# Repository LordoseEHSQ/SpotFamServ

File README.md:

# Spotify Familien Server

Privat gehostetes Familien-Musiksystem: Ein Admin verwaltet Familienprofile mit Spotify-Anbindung, Standard-Lautsprechern und RFID-Karten. Beim Scan einer Karte startet die gebundene Playlist auf dem Profil-Lautsprecher.

## Tech Stack

- **Backend:** Symfony 7.4 (LTS), PHP 8.4+ (Docker-Image/Pi: 8.5.6), Doctrine ORM 3, PostgreSQL 17
- **Frontend:** React 18, TypeScript, Vite, React Router, TanStack Query, React Hook Form
- **Infrastruktur:** Docker Compose (PHP-FPM, Nginx, PostgreSQL)

## Voraussetzungen

- Docker & Docker Compose
- PHP 8.4+ und Composer (für lokale Backend-Entwicklung ohne Docker; Docker-Stack nutzt PHP 8.5.6)
- Node 20+ und pnpm (Frontend)

Für eine frische Raspberry-Pi-Installation siehe `docs/installation.md`.

## Schnellstart

```bash
# Umgebung
cp .env.example .env
# .env anpassen: APP_SECRET, ggf. SPOTIFY_* und DATABASE_URL

# Mit Docker
make up
make migrate

# Backend lokal (ohne Docker-App-Container)
make install-backend
cd backend && php bin/console doctrine:migrations:migrate

# Frontend
make install-frontend
make frontend-dev
```

- **Backend-API:** http://localhost:8080
- **Frontend (Vite):** http://localhost:5173 (Proxy auf Backend)

## Projektstruktur

```
SpotFamServ/
├── backend/          # Symfony modularer Monolith
│   ├── config/
│   ├── migrations/
│   ├── src/Module/   # Admin, FamilyProfile, Spotify, Rfid, Scan, SetupWizard, Shared
│   └── public/
├── frontend/         # React SPA
│   └── src/
│       ├── routes/
│       ├── features/
│       ├── api/
│       └── components/
├── docker/
└── docker-compose.yml
```

## API

REST unter `/api/v1`. Siehe OpenAPI-Dokumentation (geplant) oder `backend/config/routes/`.

## Lizenz

Privat.

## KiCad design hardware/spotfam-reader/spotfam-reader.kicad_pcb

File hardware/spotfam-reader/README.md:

# SpotFam Reader – Platine Rev A

Eigene Platine für den SpotFam-Reader: **ESP32-S3-WROOM-1** direkt bestückt,
USB-C, 3,3-V-Regler, ESD-Schutz, vier Taster, Stecker für den PN532 im
Gehäusedeckel, vorbereitete Display-Anschlüsse (I2C-OLED **oder** SPI-TFT).

> **Status: platziert, nicht fertig geroutet.** Die Dateien wurden ohne KiCad
> generiert. Schaltplan, Netzliste und Pad-Zuordnung sind maschinell gegen
> `tools/design.py` geprüft, ebenso die Abstände der vorverlegten
> Versorgungsbahnen. **Routing der übrigen Netze, ERC und DRC fehlen noch.**
> Vor einer Bestellung unbedingt die Schritte unten durchgehen.

## Dateien

| Datei | Inhalt |
|---|---|
| `tools/design.py` | **Single Source of Truth**: Bauteile, Pins, Netze, LCSC-Nummern |
| `tools/generate.py` | Erzeugt alle Dateien unten (`python3 tools/generate.py`) |
| `tools/pcb.py` | Bestückungsplan (`PLACEMENT`) und vorverlegte Leiterbahnen (`ROUTES`) |
| `footprints/` | Kopien der verwendeten Footprints (KiCad-Bibliothek; ESP32-S3 aus `espressif/kicad-libraries`) |
| `spotfam-reader.kicad_sch` | Schaltplan. Netze hängen über Labels an den Pins |
| `spotfam-reader.kicad_pcb` | Platinenumriss 88,9 × 63,5 mm (Sammelkartenformat, quer), alle Bauteile platziert und mit Netzen, Antennen-Sperrzone, GND-Flächen, vorverlegte 5-V- und 3,3-V-Bahnen |
| `spotfam-reader.kicad_pro` | Projekt mit Netzklassen (Power, USB, Default) und JLCPCB-Regeln |
| `NETLIST.md` | Lesbare Netzliste zum Gegenlesen |
| `bom/jlcpcb-bom.csv` | BOM im JLCPCB-Format (nur SMD-Teile) |
| `bom/full-bom.csv` | Komplette Stückliste inkl. selbst zu lötender Teile |

Bei Änderungen an Pinbelegung oder Bauteilen gilt: `design.py` ändern und
`generate.py` ausführen. Den Schaltplan nicht von Hand umzeichnen, sonst laufen
Doku und KiCad auseinander.

**Achtung:** `generate.py` überschreibt auch `spotfam-reader.kicad_pcb`. Sobald
in KiCad geroutet wurde, ist die `.kicad_pcb` das Original. Danach Änderungen
nur noch in KiCad machen (Schaltplan → **F8**), nicht mehr neu generieren.

## GPIO-Belegung (ESP32-S3)

| Funktion | GPIO | Bemerkung |
|---|---|---|
| USB D− / D+ | 19 / 20 | Nativer USB (Flashen, Serial). Kein USB-UART-Chip nötig |
| Taster NEXT / PREV | 4 / 5 | aktiv LOW gegen GND, `INPUT_PULLUP` |
| Taster VOL+ / VOL− | 6 / 7 | aktiv LOW gegen GND, `INPUT_PULLUP` |
| I2C SDA / SCL | 8 / 9 | PN532 **und** OLED am selben Bus, 4,7 kΩ Pull-ups auf der Platine |
| PN532 IRQ / RSTO | 16 / 17 | optional, im Stecker J2 vorbereitet |
| Status-LED | 15 | über 1 kΩ, aktiv HIGH |
| SPI CS / MOSI / SCK / MISO | 10 / 11 / 12 / 13 | FSPI-Standardpins, nur für TFT |
| TFT DC / RST / BL | 14 / 21 / 47 | nur für TFT. BL direkt am GPIO (max. ca. 20 mA) |
| UART0 TX / RX | 43 / 44 | Debug-Header J5 |
| Frei (J7) | 1, 2, 18, 38 | z. B. Drehencoder |
| BOOT | 0 | Taster SW6 + 10 kΩ Pull-up |
| EN / Reset | EN | Taster SW5, RC 10 kΩ / 1 µF |

Die Strapping-Pins 3, 45 und 46 sind bewusst unbenutzt. GPIO 35–37 bleiben
frei, damit später auch Modulvarianten mit Octal-PSRAM passen.

## Steckverbinder

- **J2 PN532** (JST-XH 6-polig): 1 GND · 2 3V3 · 3 SDA · 4 SCL · 5 IRQ · 6 RSTO.
  Den HW-147 mit **3,3 V** versorgen, nicht mit 5 V: Seine I2C-Pegel hängen an
  der Versorgung, und der ESP32-S3 ist nicht 5-V-tolerant. DIP-Schalter am
  HW-147 auf I2C stellen (siehe `docs/hw0-pn532-runbook.md`).
- **J3 OLED** (Stiftleiste 4-polig): P1 · P2 · SCL · SDA.
  Bei OLED-Modulen ist die Reihenfolge von GND und VCC je nach Händler vertauscht. Deshalb:
  - **GND, VCC, SCL, SDA** (häufigste Variante): JP1 1–2 und JP2 1–2 brücken
  - **VCC, GND, SCL, SDA**: JP1 2–3 und JP2 2–3 brücken
  - Erst messen, dann brücken. Pro Jumper immer nur **eine** Seite.
- **J4 TFT** (9-polig): GND · 3V3 · SCK · MOSI · MISO · CS · DC · RST · BL.
  Nur bestücken, wenn ein SPI-TFT kommt. J3 und J4 können parallel genutzt werden.
- **J5 UART**, **J6 Panel-Taster** (parallel zu SW1–SW4, falls die Taster im
  Gehäuse sitzen statt auf der Platine), **J7 Erweiterung**: optional.

## Nächste Schritte in KiCad (7 oder 8)

Alle Bauteile sind platziert und mit Netzen versehen:
- **U1 (ESP32-S3)** mit der Antenne bündig an der Oberkante, darunter eine Sperrzone ohne Kupfer.
- **USB-C (J1)** an der linken Kante, daneben der ESD-Schutz U3.
- **Versorgung (U2, C1, C2)** oben links, **C3/C4** direkt an U1 Pin 2.
- **Taster SW1–SW4** unten, **Stecker** rechts, **TFT-Header J4** unter dem Modul.

Die 5-V-Bahn (USB → C1 → Regler) und die 3,3-V-Bahn (Regler → C2 → C3 → C4 →
Modul) sind schon verlegt, 0,6 mm breit. GND läuft über die Kupferflächen auf
beiden Lagen.

1. `spotfam-reader.kicad_pro` öffnen. Im Schaltplan den **ERC** laufen lassen.
   Hinweise zu Pin-Typen sind normal, alle Pins sind als `passive` definiert.
2. Im Leiterplatteneditor **Freerouting** installieren:
   *Werkzeuge → Plugin and Content Manager → Plugins → „Freerouting“*.
   Danach *Werkzeuge → Externe Plugins → Freerouting* starten. Die
   vorhandenen Bahnen bleiben erhalten.
3. **B** drücken (Zonen füllen), dann **DRC** (*Prüfen → Designregelprüfung*).
4. Ergebnis ansehen und kritische Stellen gegebenenfalls von Hand nachziehen:
   - **USB D+/D−** (J1 → U3 → U1): möglichst kurz, beide Leitungen nebeneinander.
     Der ESP32-S3 kann nur USB Full Speed (12 Mbit/s). Impedanz und
     Längenausgleich sind dort unkritisch, ein paar Millimeter Umweg schaden nicht.
   - Keine Bahn unter der Antenne. Die Sperrzone verhindert das ohnehin.
   - Möglichst wenige Durchkontaktierungen in der GND-Fläche direkt unter dem Modul.
5. Fertigungsdaten erzeugen (siehe unten).

Optional zur Kontrolle: *Werkzeuge → Update PCB from Schematic (F8)*. Es
sollte nichts ändern. Das Modul-Footprint stammt aus der Espressif-Bibliothek,
trägt aber die Bibliotheks-ID `RF_Module:ESP32-S3-WROOM-1`. F8 darf es nicht
ersetzen, also **„Replace footprints with those specified in symbol“ nicht
anhaken.**

## Bestellung bei JLCPCB

**Leiterplatte:** 2 Lagen, 1,6 mm, HASL bleifrei. Gerber über
*Datei → Fertigungsausgaben → Gerber* (Lagen F/B.Cu, F/B.Mask, F/B.SilkS,
F/B.Paste, Edge.Cuts) plus Bohrdatei (Excellon, mm, PTH/NPTH getrennt).
Alles zippen und hochladen.

**SMD-Bestückung (PCBA):** sinnvoll für U1, U2, U3, J1, alle R/C/LEDs.
- BOM: `bom/jlcpcb-bom.csv`
- CPL (Bestückungsdatei): *Datei → Fertigungsausgaben → Bauteilpositionen*
  (CSV, mm, nur Oberseite).
  Spalten für JLCPCB umbenennen: `Designator, Mid X, Mid Y, Layer, Rotation`.
- **Die LCSC-Nummern vor der Bestellung im JLCPCB-Katalog prüfen** (Bestand,
  Basic- oder Extended-Part). Gesichert ist C2913204 für das ESP32-S3-WROOM-1-N8R2.
  Die übrigen Nummern sind gängige Standardteile, aber nicht einzeln gegen den
  aktuellen Katalog geprüft.
- Die Drehung der Bauteile in der JLCPCB-Vorschau kontrollieren, vor allem bei
  U2, U3 und J1. Abweichende Drehungen zwischen KiCad und JLCPCB sind der
  häufigste Bestückungsfehler.

**Selbst löten:** Taster SW1–SW6 (THT 6×6 mm), J2 (JST-XH), Stiftleisten
J3–J7, Lötbrücken JP1/JP2.

## Firmware-Anpassungen für den ESP32-S3

Die aktuelle Firmware (`firmware/spotfam_reader`, 0.10.x) ist auf den
ESP32-WROOM-32 ausgelegt. Für diese Platine sind nötig:

1. `config.h`: Pins gemäß Tabelle oben (`PIN_PN532_SDA 8`, `PIN_PN532_SCL 9`,
   `PIN_BTN_NEXT 4`, `PIN_BTN_PREV 5`, `PIN_BTN_VOL_UP 6`,
   `PIN_BTN_VOL_DOWN 7`, `PIN_LED 15`). Optional `PIN_PN532_IRQ 16` und
   `PIN_PN532_RST 17`.
2. `FIRMWARE_BOARD` auf einen neuen Board-Schlüssel setzen, z. B. `esp32-s3`,
   damit OTA-Manifeste nicht auf die falsche Hardware gehen.
3. Build: FQBN `esp32:esp32:esp32s3` mit `CDCOnBoot=cdc`, sonst kommt
   `Serial` nicht über USB-C. Der Release-Workflow
   (`.github/workflows/release-firmware.yml`) braucht einen zweiten Build-Job.
4. Backend: Board `esp32-s3` im Firmware-Manifest zulassen, sonst kommt
   `unsupported_board` (422). Die Flash-Station erkennt den nativen USB
   des S3 bereits (`303A:1001` in `flash_agent/detect.py`).

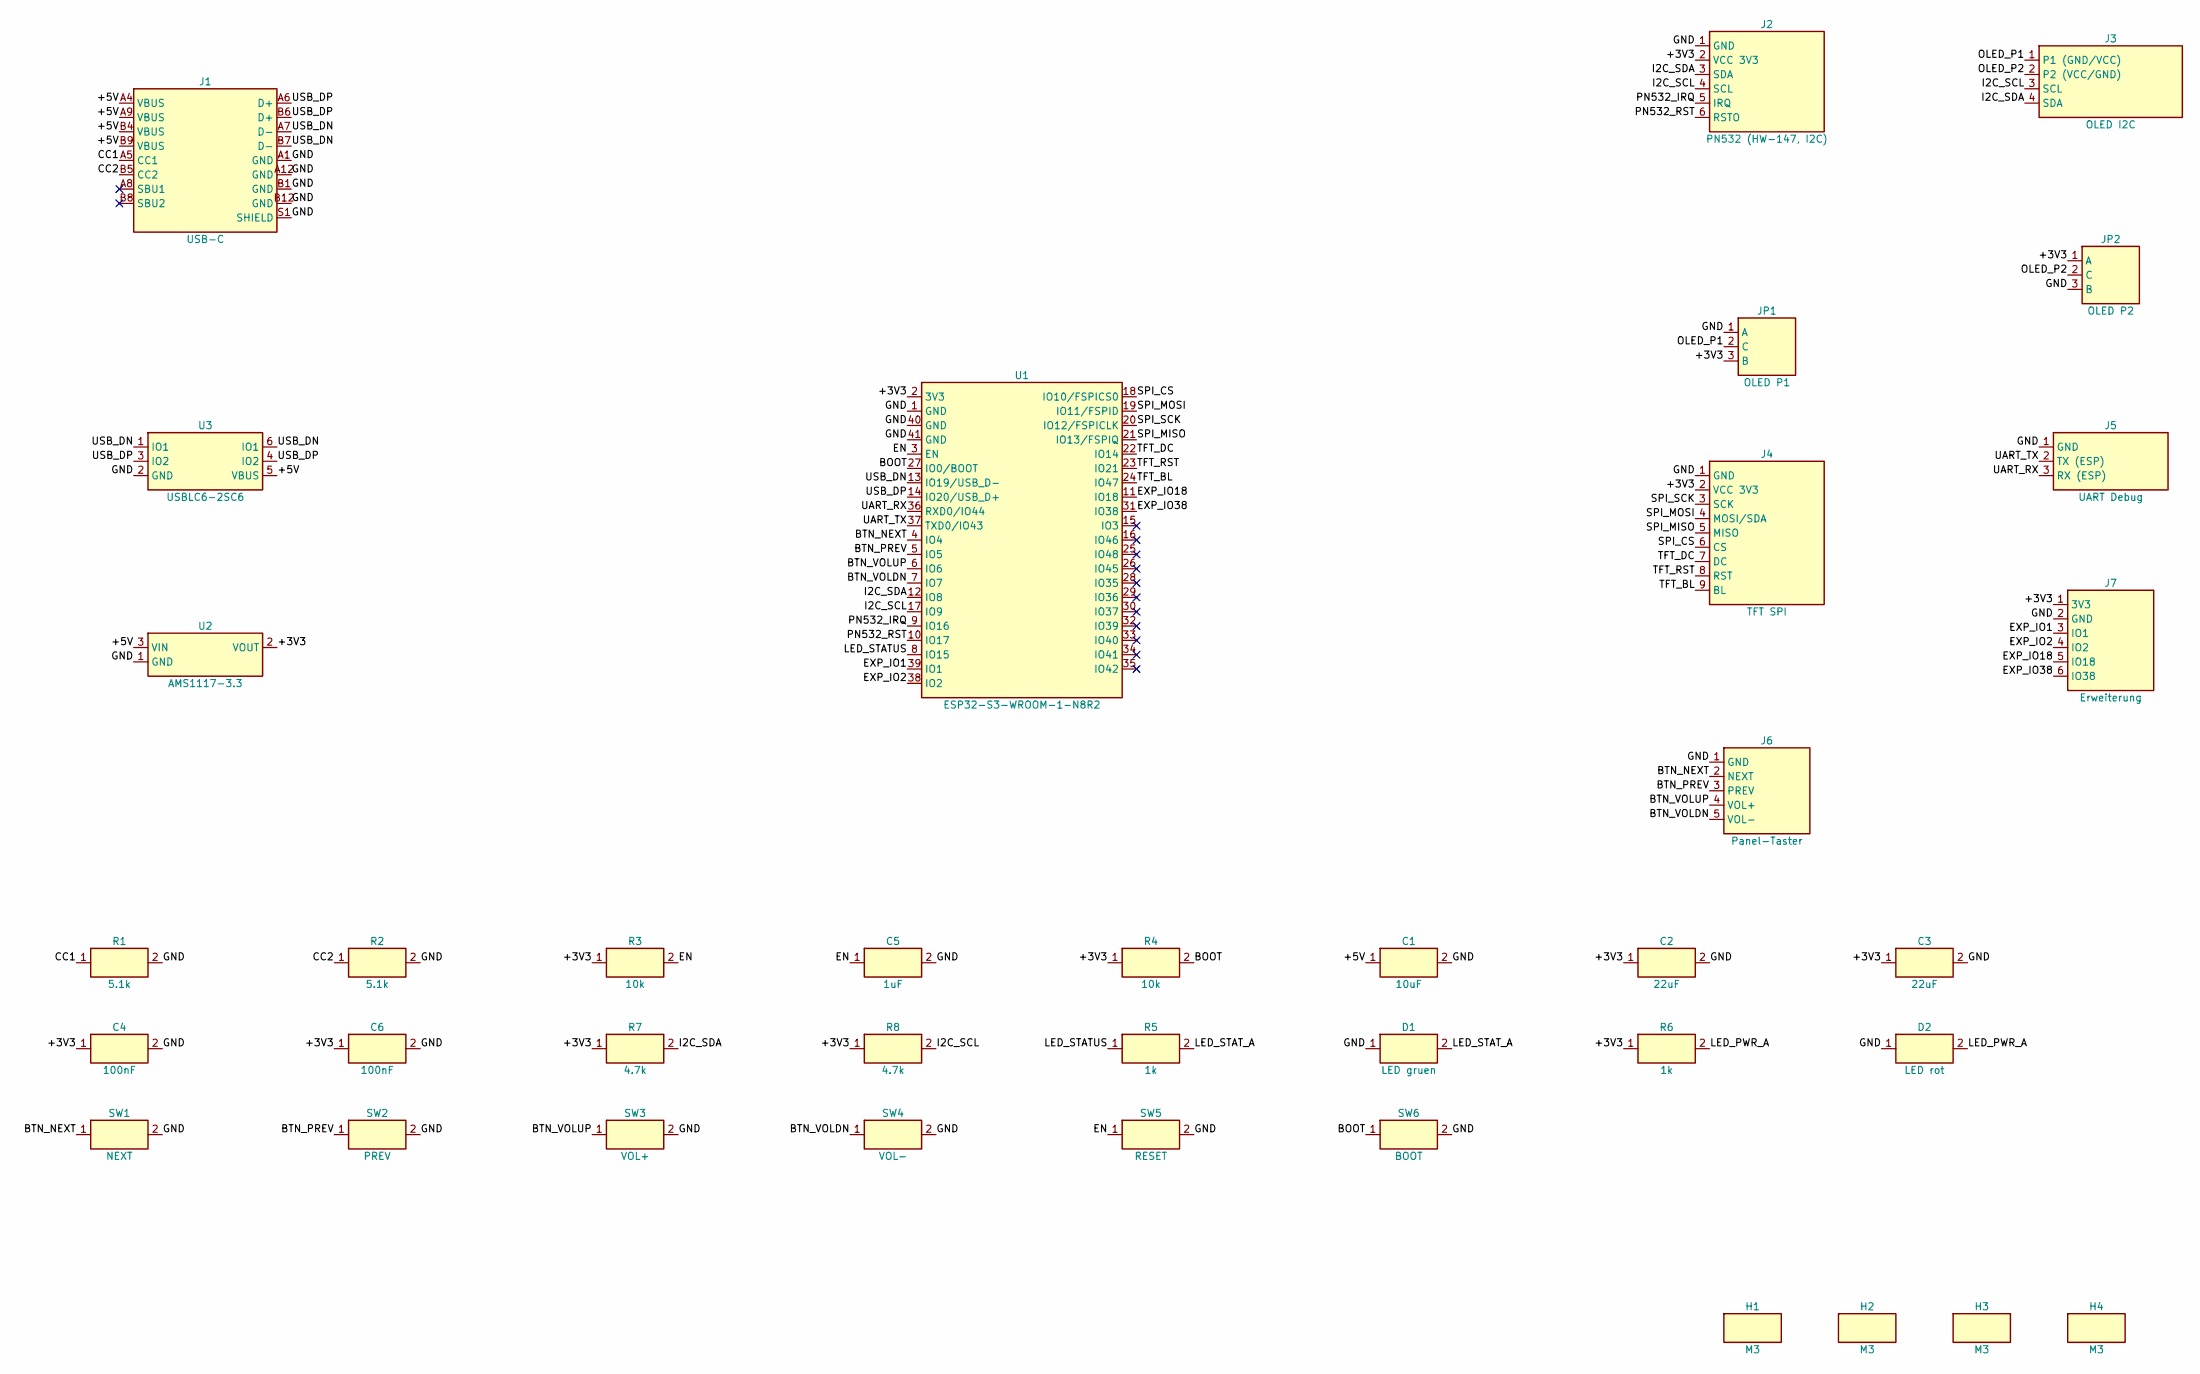
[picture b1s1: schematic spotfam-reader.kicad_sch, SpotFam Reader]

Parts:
C1: 10uF; C_0805_2012Metric; LCSC C15850
C2, C3: 22uF; C_0805_2012Metric; LCSC C45783
C4, C6: 100nF; C_0603_1608Metric; LCSC C14663
C5: 1uF; C_0603_1608Metric; LCSC C15849
D1: LED gruen; LED_0603_1608Metric; LCSC C72043
D2: LED rot; LED_0603_1608Metric; LCSC C2286
H1, H2, H3, H4: M3; MountingHole_3.2mm_M3
J1: USB-C; USB_C_Receptacle_HRO_TYPE-C-31-M-12; LCSC C165948
J2: PN532 (HW-147, I2C); JST_XH_B6B-XH-A_1x06_P2.50mm_Vertical
J3: OLED I2C; PinHeader_1x04_P2.54mm_Vertical
J4: TFT SPI; PinHeader_1x09_P2.54mm_Vertical
J5: UART Debug; PinHeader_1x03_P2.54mm_Vertical
J6: Panel-Taster; PinHeader_1x05_P2.54mm_Vertical
J7: Erweiterung; PinHeader_1x06_P2.54mm_Vertical
JP1: OLED P1; SolderJumper-3_P1.3mm_Open_RoundedPad1.0x1.5mm
JP2: OLED P2; SolderJumper-3_P1.3mm_Open_RoundedPad1.0x1.5mm
R1, R2: 5.1k; R_0603_1608Metric; LCSC C23186
R3, R4: 10k; R_0603_1608Metric; LCSC C25804
R5, R6: 1k; R_0603_1608Metric; LCSC C21190
R7, R8: 4.7k; R_0603_1608Metric; LCSC C23162
SW1: NEXT; SW_PUSH_6mm
SW2: PREV; SW_PUSH_6mm
SW3: VOL+; SW_PUSH_6mm
SW4: VOL-; SW_PUSH_6mm
SW5: RESET; SW_PUSH_6mm
SW6: BOOT; SW_PUSH_6mm
U1: ESP32-S3-WROOM-1-N8R2; ESP32-S3-WROOM-1; LCSC C2913204
U2: AMS1117-3.3; SOT-223-3_TabPin2; LCSC C6186
U3: USBLC6-2SC6; SOT-23-6; LCSC C7519

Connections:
+3V3: C2.1, C3.1, C4.1, C6.1, J2.2 (VCC 3V3), J4.2 (VCC 3V3), J7.1 (3V3), JP1.3 (B), JP2.1 (A), R3.1, R4.1, R6.1, R7.1, R8.1, U1.2 (3V3), U2.2 (VOUT)
+5V: C1.1, J1.A4 (VBUS), J1.A9 (VBUS), J1.B4 (VBUS), J1.B9 (VBUS), U2.3 (VIN), U3.5 (VBUS)
BOOT: R4.2, SW6.1, U1.27 (IO0/BOOT)
BTN_NEXT: J6.2 (NEXT), SW1.1, U1.4 (IO4)
BTN_PREV: J6.3 (PREV), SW2.1, U1.5 (IO5)
BTN_VOLDN: J6.5 (VOL-), SW4.1, U1.7 (IO7)
BTN_VOLUP: J6.4 (VOL+), SW3.1, U1.6 (IO6)
CC1: J1.A5 (CC1), R1.1
CC2: J1.B5 (CC2), R2.1
EN: C5.1, R3.2, SW5.1, U1.3 (EN)
EXP_IO1: J7.3 (IO1), U1.39 (IO1)
EXP_IO2: J7.4 (IO2), U1.38 (IO2)
EXP_IO18: J7.5 (IO18), U1.11 (IO18)
EXP_IO38: J7.6 (IO38), U1.31 (IO38)
GND: C1.2, C2.2, C3.2, C4.2, C5.2, C6.2, D1.1 (K), D2.1 (K), J1.A1 (GND), J1.A12 (GND), J1.B1 (GND), J1.B12 (GND), J1.S1 (SHIELD), J2.1 (GND), J4.1 (GND), J5.1 (GND), J6.1 (GND), J7.2 (GND), JP1.1 (A), JP2.3 (B), R1.2, R2.2, SW1.2, SW2.2, SW3.2, SW4.2, SW5.2, SW6.2, U1.1 (GND), U1.40 (GND), U1.41 (GND), U2.1 (GND), U3.2 (GND)
I2C_SCL: J2.4 (SCL), J3.3 (SCL), R8.2, U1.17 (IO9)
I2C_SDA: J2.3 (SDA), J3.4 (SDA), R7.2, U1.12 (IO8)
LED_PWR_A: D2.2 (A), R6.2
LED_STATUS: R5.1, U1.8 (IO15)
LED_STAT_A: D1.2 (A), R5.2
OLED_P1: J3.1 (P1 (GND/VCC)), JP1.2 (C)
OLED_P2: J3.2 (P2 (VCC/GND)), JP2.2 (C)
PN532_IRQ: J2.5 (IRQ), U1.9 (IO16)
PN532_RST: J2.6 (RSTO), U1.10 (IO17)
SPI_CS: J4.6 (CS), U1.18 (IO10/FSPICS0)
SPI_MISO: J4.5 (MISO), U1.21 (IO13/FSPIQ)
SPI_MOSI: J4.4 (MOSI/SDA), U1.19 (IO11/FSPID)
SPI_SCK: J4.3 (SCK), U1.20 (IO12/FSPICLK)
TFT_BL: J4.9 (BL), U1.24 (IO47)
TFT_DC: J4.7 (DC), U1.22 (IO14)
TFT_RST: J4.8 (RST), U1.23 (IO21)
UART_RX: J5.3 (RX (ESP)), U1.36 (RXD0/IO44)
UART_TX: J5.2 (TX (ESP)), U1.37 (TXD0/IO43)
USB_DN: J1.A7 (D-), J1.B7 (D-), U1.13 (IO19/USB_D-), U3.1 (IO1), U3.6 (IO1)
USB_DP: J1.A6 (D+), J1.B6 (D+), U1.14 (IO20/USB_D+), U3.3 (IO2), U3.4 (IO2)

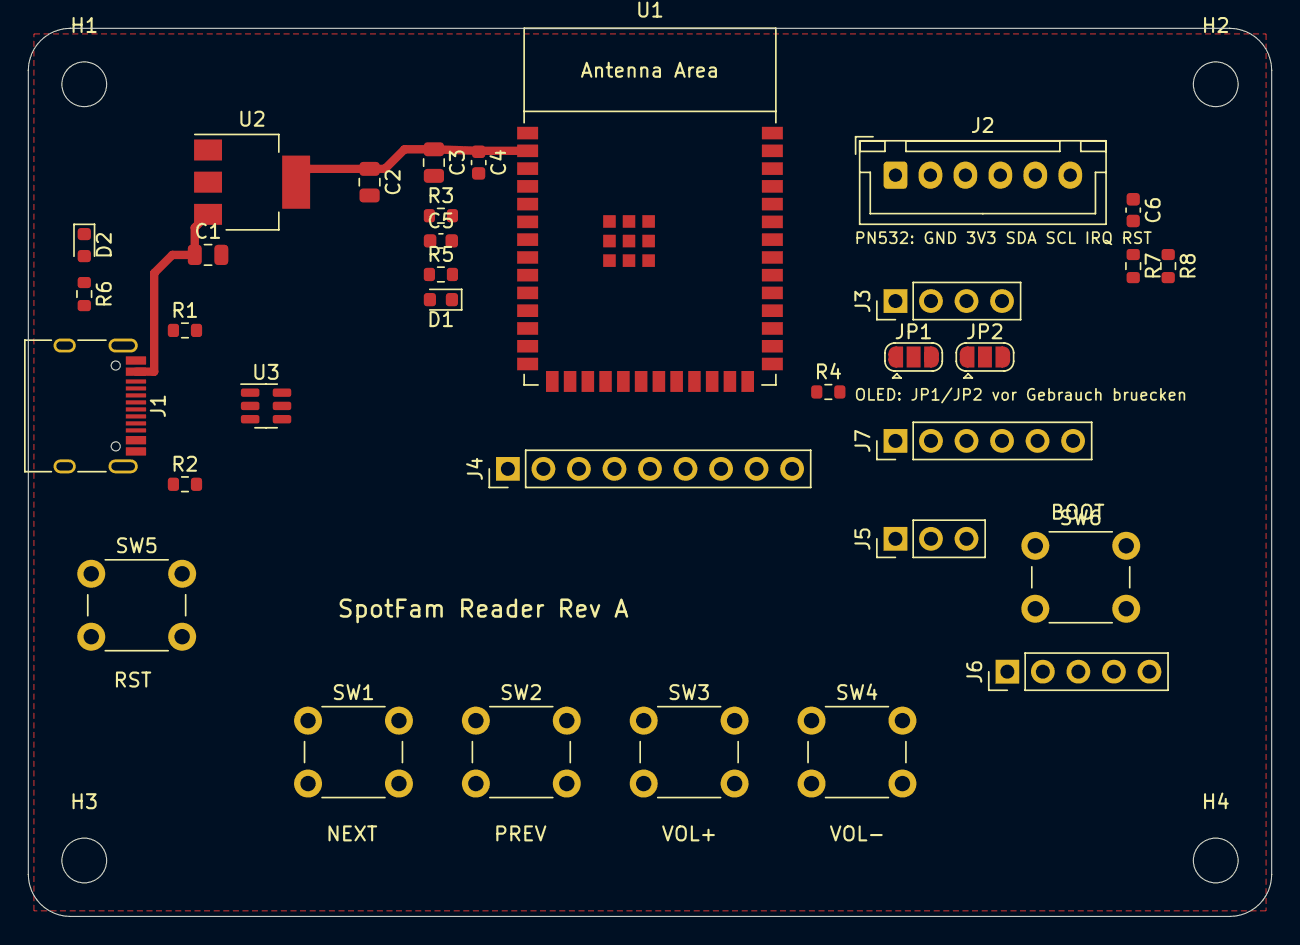
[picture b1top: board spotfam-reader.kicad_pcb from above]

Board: 2 copper layers, 88.9 x 63.5 mm, 38 parts (0 on the bottom side), 35 nets.

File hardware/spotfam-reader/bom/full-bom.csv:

Menge,Referenzen,Wert,MPN,Footprint,LCSC,Bestueckung
1,C1,10uF,,Capacitor_SMD:C_0805_2012Metric,C15850,JLCPCB SMT
2,"C2,C3",22uF,,Capacitor_SMD:C_0805_2012Metric,C45783,JLCPCB SMT
2,"C4,C6",100nF,,Capacitor_SMD:C_0603_1608Metric,C14663,JLCPCB SMT
1,C5,1uF,,Capacitor_SMD:C_0603_1608Metric,C15849,JLCPCB SMT
1,D1,LED gruen,,LED_SMD:LED_0603_1608Metric,C72043,JLCPCB SMT
1,D2,LED rot,,LED_SMD:LED_0603_1608Metric,C2286,JLCPCB SMT
1,J1,USB-C,TYPE-C-31-M-12,Connector_USB:USB_C_Receptacle_HRO_TYPE-C-31-M-12,C165948,JLCPCB SMT
1,J2,"PN532 (HW-147, I2C)",,Connector_JST:JST_XH_B6B-XH-A_1x06_P2.50mm_Vertical,,selbst loeten
1,J3,OLED I2C,,Connector_PinHeader_2.54mm:PinHeader_1x04_P2.54mm_Vertical,,selbst loeten
1,J4,TFT SPI,,Connector_PinHeader_2.54mm:PinHeader_1x09_P2.54mm_Vertical,,selbst loeten
1,J5,UART Debug,,Connector_PinHeader_2.54mm:PinHeader_1x03_P2.54mm_Vertical,,selbst loeten
1,J6,Panel-Taster,,Connector_PinHeader_2.54mm:PinHeader_1x05_P2.54mm_Vertical,,selbst loeten
1,J7,Erweiterung,,Connector_PinHeader_2.54mm:PinHeader_1x06_P2.54mm_Vertical,,selbst loeten
1,JP1,OLED P1,,Jumper:SolderJumper-3_P1.3mm_Open_RoundedPad1.0x1.5mm,,selbst loeten
1,JP2,OLED P2,,Jumper:SolderJumper-3_P1.3mm_Open_RoundedPad1.0x1.5mm,,selbst loeten
2,"R1,R2",5.1k,,Resistor_SMD:R_0603_1608Metric,C23186,JLCPCB SMT
2,"R3,R4",10k,,Resistor_SMD:R_0603_1608Metric,C25804,JLCPCB SMT
2,"R5,R6",1k,,Resistor_SMD:R_0603_1608Metric,C21190,JLCPCB SMT
2,"R7,R8",4.7k,,Resistor_SMD:R_0603_1608Metric,C23162,JLCPCB SMT
1,SW1,NEXT,,Button_Switch_THT:SW_PUSH_6mm,,selbst loeten
1,SW2,PREV,,Button_Switch_THT:SW_PUSH_6mm,,selbst loeten
1,SW3,VOL+,,Button_Switch_THT:SW_PUSH_6mm,,selbst loeten
1,SW4,VOL-,,Button_Switch_THT:SW_PUSH_6mm,,selbst loeten
1,SW5,RESET,,Button_Switch_THT:SW_PUSH_6mm,,selbst loeten
1,SW6,BOOT,,Button_Switch_THT:SW_PUSH_6mm,,selbst loeten
1,U1,ESP32-S3-WROOM-1-N8R2,ESP32-S3-WROOM-1-N8R2,RF_Module:ESP32-S3-WROOM-1,C2913204,JLCPCB SMT
1,U2,AMS1117-3.3,AMS1117-3.3,Package_TO_SOT_SMD:SOT-223-3_TabPin2,C6186,JLCPCB SMT
1,U3,USBLC6-2SC6,USBLC6-2SC6,Package_TO_SOT_SMD:SOT-23-6,C7519,JLCPCB SMT

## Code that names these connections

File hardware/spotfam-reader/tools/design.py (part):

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    two_pin("C4", "100nF", C0603, "+3V3", "GND", "C14663", symbol="C", note="Modul HF, nah an U1 Pin 2"),
    two_pin("C6", "100nF", C0603, "+3V3", "GND", "C14663", symbol="C", note="Nah an J2 (PN532)"),
    # I2C-Pull-ups (Bus geht per Kabel in den Deckel)
    two_pin("R7", "4.7k", R0603, "+3V3", "I2C_SDA", "C23162", note="I2C SDA Pull-up"),
    two_pin("R8", "4.7k", R0603, "+3V3", "I2C_SCL", "C23162", note="I2C SCL Pull-up"),
    # LEDs
    two_pin("R5", "1k", R0603, "LED_STATUS", "LED_STAT_A", "C21190"),
    two_pin("D1", "LED gruen", LED0603, "GND", "LED_STAT_A", "C72043", symbol="LED", names=("K", "A"), note="Status (IO15)"),
    two_pin("R6", "1k", R0603, "+3V3", "LED_PWR_A", "C21190"),
    two_pin("D2", "LED rot", LED0603, "GND", "LED_PWR_A", "C2286", symbol="LED", names=("K", "A"), note="Power"),
    # Taster - THT 6x6 mm, selbst loeten
    two_pin("SW1", "NEXT", SW6MM, "BTN_NEXT", "GND", assembly="Hand", symbol="SW"),
    two_pin("SW2", "PREV", SW6MM, "BTN_PREV", "GND", assembly="Hand", symbol="SW"),
    two_pin("SW3", "VOL+", SW6MM, "BTN_VOLUP", "GND", assembly="Hand", symbol="SW"),
    two_pin("SW4", "VOL-", SW6MM, "BTN_VOLDN", "GND", assembly="Hand", symbol="SW"),
    two_pin("SW5", "RESET", SW6MM, "EN", "GND", assembly="Hand", symbol="SW"),
    two_pin("SW6", "BOOT", SW6MM, "BOOT", "GND", assembly="Hand", symbol="SW"),
]
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
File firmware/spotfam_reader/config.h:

// ---------------------------------------------------------------------------
// config.h  –  Hardware-Pinout & Verhalten (kein Geheimnis, darf ins Repo)
// Board-Default: ESP32-WROOM-32 DevKit (FQBN esp32:esp32:esp32)
// ---------------------------------------------------------------------------
#pragma once

// --- PN532/HW-147 (I2C) -----------------------------------------------------
// Zielhardware: dasselbe PN532/HW-147-Modul wie am Pi.
#define PIN_PN532_SDA   21
#define PIN_PN532_SCL   22
#define PIN_PN532_IRQ   -1   // -1 = I2C-Polling ohne IRQ-Draht
#define PIN_PN532_RST   -1   // -1 = Reset nicht verdrahtet

// --- Taster (gegen GND, interner Pull-up; aktiv LOW) -----------------------
// GPIO0/BOOT darf hier nie verwendet werden.
#define SPOTFAM_ENABLE_BUTTONS   1
#define PIN_BTN_NEXT             25
#define PIN_BTN_PREV             26
#define PIN_BTN_VOL_UP           32
#define PIN_BTN_VOL_DOWN         33

// --- Status-LED (onboard) --------------------------------------------------
#define PIN_LED         2

// --- Firmware/OTA -----------------------------------------------------------
#define FIRMWARE_VERSION "0.10.2"
#define FIRMWARE_BOARD   "esp32-wroom-32"
#define DEFAULT_FW_CHANNEL "stable"

// --- Verhalten -------------------------------------------------------------
#define SERIAL_BAUD            115200
#define WIFI_CONNECT_TIMEOUT_MS 20000  // max. Wartezeit auf WLAN beim Start
#define HTTP_TIMEOUT_MS         8000   // pro Request
#define BUTTON_DEBOUNCE_MS      250    // Entprellung Taster
#define SCAN_COOLDOWN_MS        1500   // lokale Sperre nach Karten-Scan
                                       // (Backend entprellt zusaetzlich 5 s)
#define CARD_REMOVE_DEBOUNCE_MS 1500   // Karte muss mind. 1,5 s weg sein → Pause
#define PN532_READ_TIMEOUT_MS   1000
#define PN532_REINIT_MS          5000
#define BACKEND_RETRY_MS        5000
#define OTA_CHECK_INTERVAL_MS   3600000UL

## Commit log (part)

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2026-03-18 feat: initialer Commit – SpotFamServ MVP mit professionellem Admin-UI
    Vollständiger erster Commit des SpotFamServ-Projekts inkl. aller bisherigen
    Entwicklungsschritte:
    Backend (Symfony 7.2, PHP 8.3, Doctrine ORM 3, PostgreSQL 15):
    - Hexagonale Architektur (Domain / Application / Infrastructure)
    - Module: FamilyProfile, Spotify (OAuth, Playback, Devices), Rfid,
    Scan, SetupWizard, Device (Governance), ActivityLog
2026-03-19 feat: Mini-Spotify Musikarbeitsbereich + Spotify-Governance-Erweiterungen
    ## Neue Features
    - Profilgebundener Musikarbeitsbereich (Musik-Tab im Teilnehmerprofil)
    - Playlist-Liste mit Suche und Erstell-Dialog
    - Playlist-Detail mit Track-Anzeige
    - Spotify-Inhaltssuche (Tracks + Playlists)
    - Mini-Player mit Playback-Steuerung (Play/Pause/Next/Prev)
2026-06-02 Sprint 3 (Interim v0.2.4): Reader-Lifecycle, Pi-Leser, Pro-Reader-Keys, Scan-to-Create
    Interim-Release des Sprint-3-Branches nach main (D-S3b). Enthält:
    - #32 Reader→Box-Mapping / Reader-Lifecycle
    - #34 Pi-Leser (PN532) + Scan-to-Create am Profil + globaler UID-Lookup
    - #35 Pro-Reader-API-Keys
    - #36 Terminologie Wobie→Connect
    CI grün (PHPStan L8, PHPUnit, oasdiff non-breaking, Frontend, Trivy).
2026-06-03 feat(reader): add ESP provisioning claim flow
    Introduce a short-lived reader claim contract and OTA manifest baseline so ESP onboarding can progress without changing existing scan/control APIs.
2026-06-03 fix(api): preserve RFID cards response schema
    Restore the existing RFID card list success response so the additive reader provisioning API does not trip the breaking-change gate.
2026-06-03 fix(api): generate RFID cards response schema
    Add the OpenAPI source annotation so the API drift job preserves the existing RFID card list success response after regenerating the spec.
2026-06-03 feat(reader): add ESP provisioning claim flow
    Add the software-side ESP reader provisioning baseline: short-lived claims, per-reader key issuance, firmware manifest contract, Reader UI onboarding, Dry-Run/model gates, and documentation. HW-0 rem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
2026-06-03 ci(firmware): add ESP32 compile gate
    Add a reproducible arduino-cli compile job for the existing reader firmware baseline so firmware regressions are caught before the PN532 hardware phase.
2026-06-03 ci(firmware): add ESP32 compile gate
    Add a reproducible arduino-cli compile gate for the existing ESP32 reader firmware baseline. This closes the firmware build reproducibility part of the plan, while HW-0 and the PN532/Captive Portal/N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
2026-06-05 Sprint 06: Reader-Station UX + System-Config-DB + Flash-Zeit-NVS (v0.6.0)
    Closes #63 #64 #65. Scope A+B+C; D/E → Sprint 08 (PN532). Details: docs/sprints/sprint-06.md
2026-06-07 docs: add Raspberry Pi installation guide
    Dokumentiert die frische SpotFamServ-Installation vom Pi-OS bis zum Setup, damit Betrieb und Ersteinrichtung nicht mehr aus verstreuten Runbooks rekonstruiert werden müssen.
2026-06-07 docs: add Raspberry Pi installation guide (#76)
    Dokumentiert die frische SpotFamServ-Installation vom Pi-OS bis zum Setup, damit Betrieb und Ersteinrichtung nicht mehr aus verstreuten Runbooks rekonstruiert werden müssen.
2026-06-09 feat(sprint-08): PN532 Reader-Firmware v0.8.2, OTA & Reader Admin UI
    Squash-Merge Sprint 08. Schließt alle Deliverables: ESP32 PN532-Firmware, Reader-Diagnostik-Migration, Reader-Zentrale UI, Onboarding-Wizard.
2026-06-09 feat(sprint-09): Audio-UX Härtung, Reader-Lifecycle, FPM-Tuning, Deploy-Härtung (v0.9.0)
    Closes #78, #79, #80, #81, #82
2026-06-09 feat(sprint-10): Reader Lifecycle Cockpit (v0.10.0)
    WP-1–5: last_ip/minutes_since_seen, Zeitstempel-Badge, setup-pi.sh, release-firmware.yml, Firmware-Station-UX
